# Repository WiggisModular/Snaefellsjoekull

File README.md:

** Prodution files out of date, pots go the wrong way round. **

A simple modular eurorack stereo mixer.

## Modules

### panMonoCannel

* Panning mono channel

### MainNoFx

* A main out, 2 separate pots for out Volume.
* No FX send and return 

## Production Files and Documentation

See release tab

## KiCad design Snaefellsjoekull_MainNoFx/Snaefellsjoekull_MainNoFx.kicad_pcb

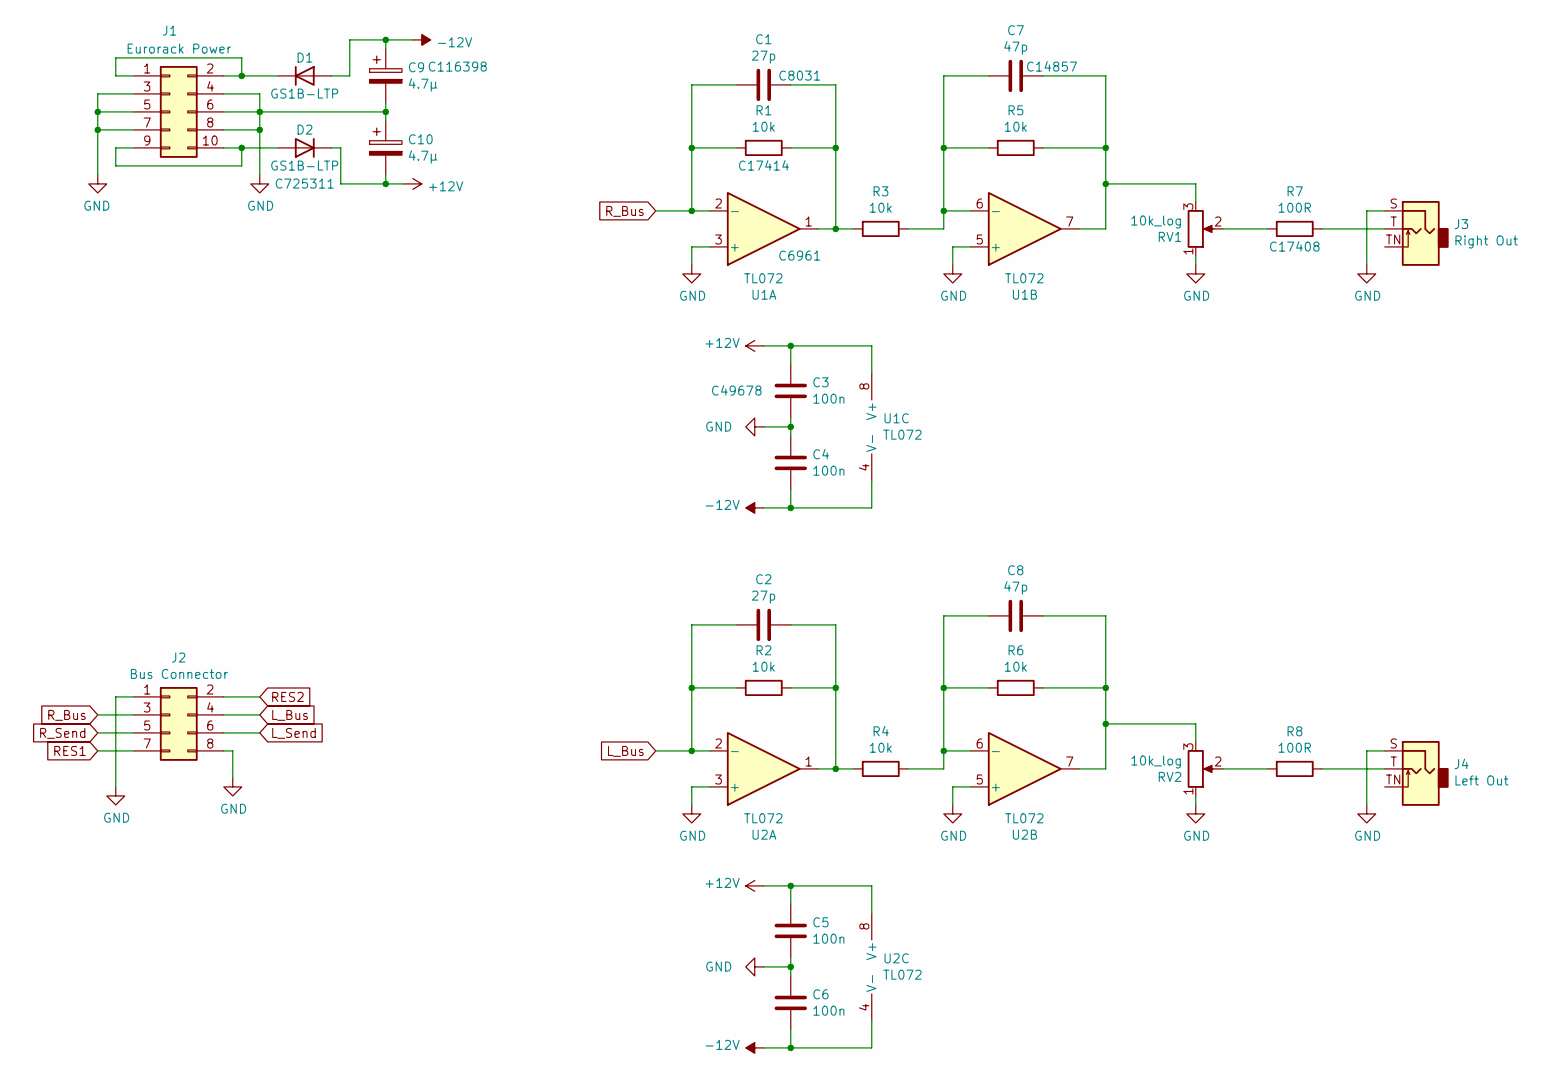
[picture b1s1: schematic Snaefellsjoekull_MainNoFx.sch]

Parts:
C1, C2: 27p; C_0805_2012Metric_Pad1.18x1.45mm_HandSolder; LCSC C8031
C3, C4, C5, C6: 100n; C_0805_2012Metric_Pad1.18x1.45mm_HandSolder; LCSC C49678
C7, C8: 47p; C_0805_2012Metric_Pad1.18x1.45mm_HandSolder; LCSC C14857
C9, C10: 4.7µ; CP_Elec_4x5.8; LCSC C116398
D1, D2: GS1B-LTP; D_SMA-SMB_Universal_Handsoldering; LCSC C725311
J1: Eurorack Power; PinHeader_2x05_P2.54mm_Vertical
J2: Bus Connector; PinHeader_2x04_P2.54mm_Vertical
J3: Right Out; Jack_3.5mm_QingPu_WQP-PJ398SM_Vertical_CircularHoles
J4: Left Out; Jack_3.5mm_QingPu_WQP-PJ398SM_Vertical_CircularHoles
R1, R2, R3, R4, R5, R6: 10k; R_0805_2012Metric_Pad1.20x1.40mm_HandSolder; LCSC C17414
R7, R8: 100R; R_0805_2012Metric_Pad1.20x1.40mm_HandSolder; LCSC C17408
RV1, RV2: 10k_log; Potentiometer_Alpha_RD901F-40-00D_Single_Vertical_CircularH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
U1, U2: TL072; SOIC-8_3.9x4.9mm_P1.27mm; LCSC C6961

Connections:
+12V: C3.1, C5.1, C10.2, D2.1 (K), U1.8 (V+), U2.8 (V+)
-12V: C4.2, C6.2, C9.1, D1.2 (A), U1.4 (V-), U2.4 (V-)
GND: C3.2, C4.1, C5.2, C6.1, C9.2, C10.1, J1.3, J1.4, J1.5, J1.6, J1.7, J1.8, J2.1, J2.8, J3.S, J4.S, RV1.1, RV2.1, U1.3 (+), U1.5 (+), U2.3 (+), U2.5 (+)
L_Bus: C2.1, J2.4, R2.2, U2.2 (-)
L_Send: J2.6
unnamed: C1.2, R1.1, R3.2, U1.1
unnamed: C2.2, R2.1, R4.2, U2.1
unnamed: C7.1, R3.1, R5.2, U1.6 (-)
unnamed: C7.2, R5.1, RV1.3, U1.7
unnamed: C8.1, R4.1, R6.2, U2.6 (-)
unnamed: C8.2, R6.1, RV2.3, U2.7
unnamed: D1.1 (K), J1.1, J1.2
unnamed: D2.2 (A), J1.9, J1.10
unnamed: J3.T, R7.1
unnamed: J4.T, R8.1
unnamed: R7.2, RV1.2
unnamed: R8.2, RV2.2
RES1: J2.7
RES2: J2.2
R_Bus: C1.1, J2.3, R1.2, U1.2 (-)
R_Send: J2.5

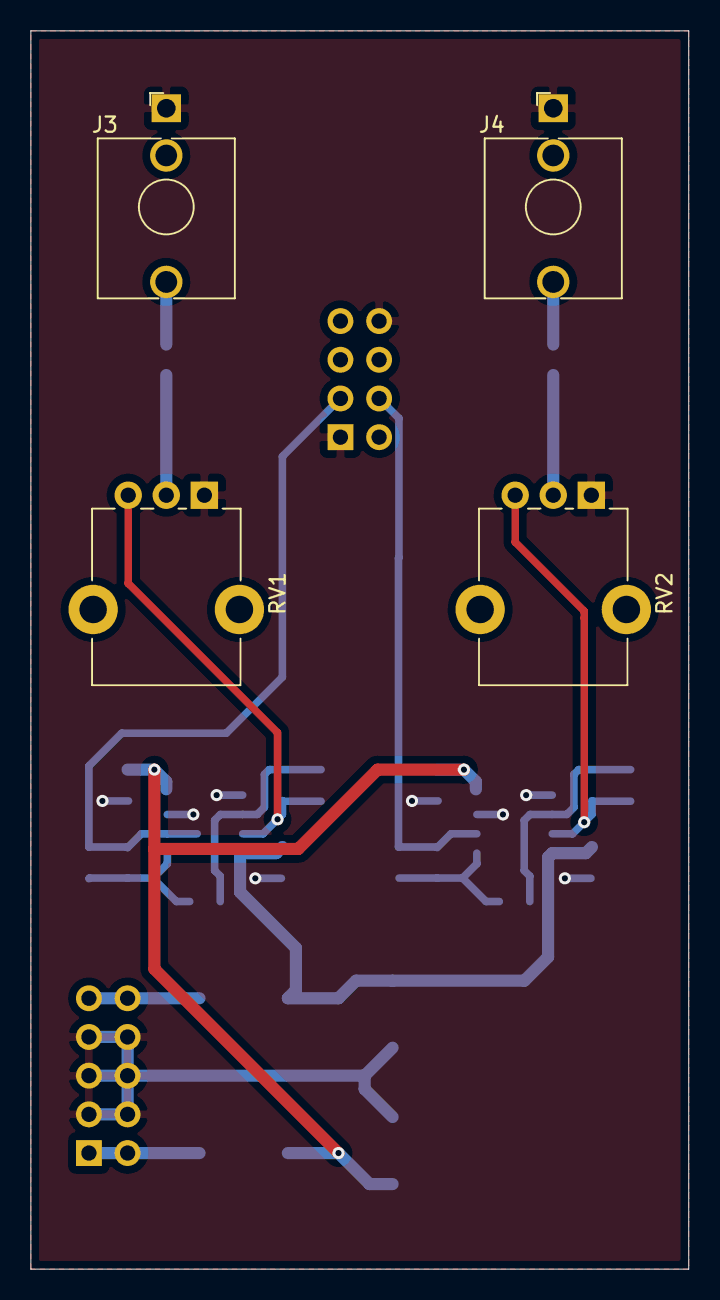
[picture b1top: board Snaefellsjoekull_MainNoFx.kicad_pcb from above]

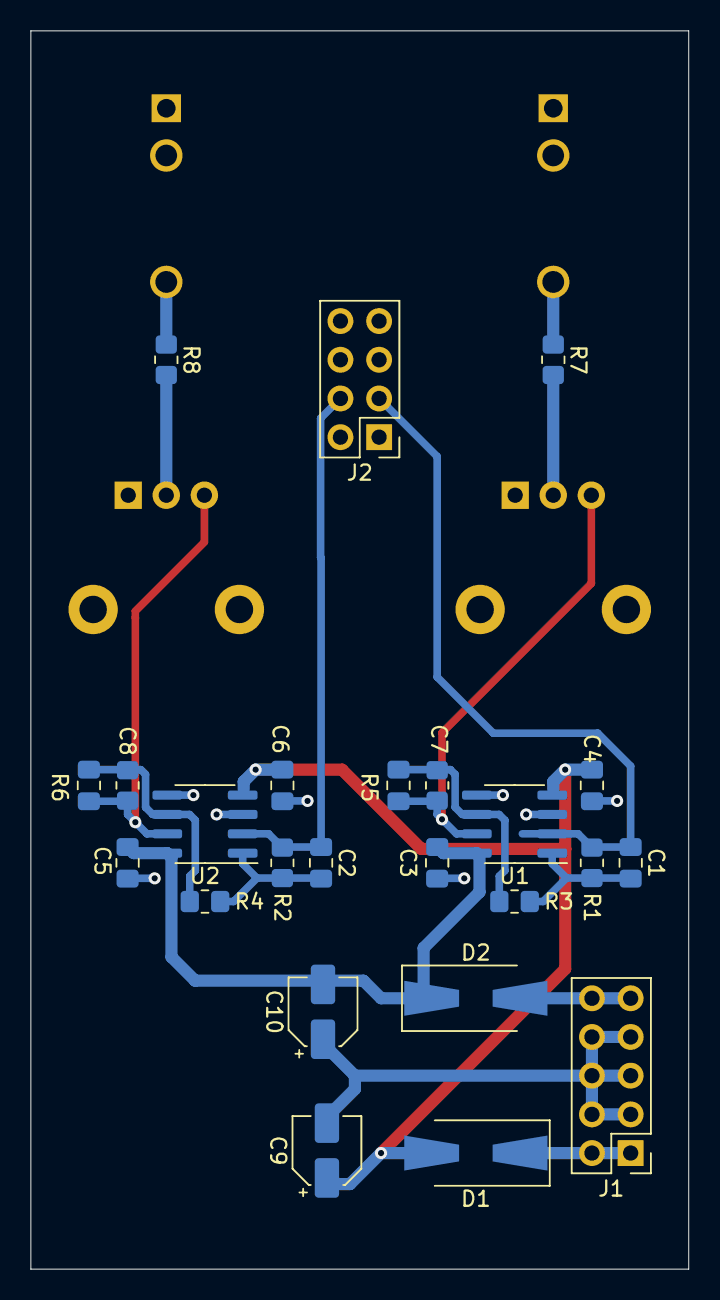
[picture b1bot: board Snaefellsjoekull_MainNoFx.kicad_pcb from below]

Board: 2 copper layers, 43.2 x 81.3 mm, 28 parts (24 on the bottom side), 17 nets.

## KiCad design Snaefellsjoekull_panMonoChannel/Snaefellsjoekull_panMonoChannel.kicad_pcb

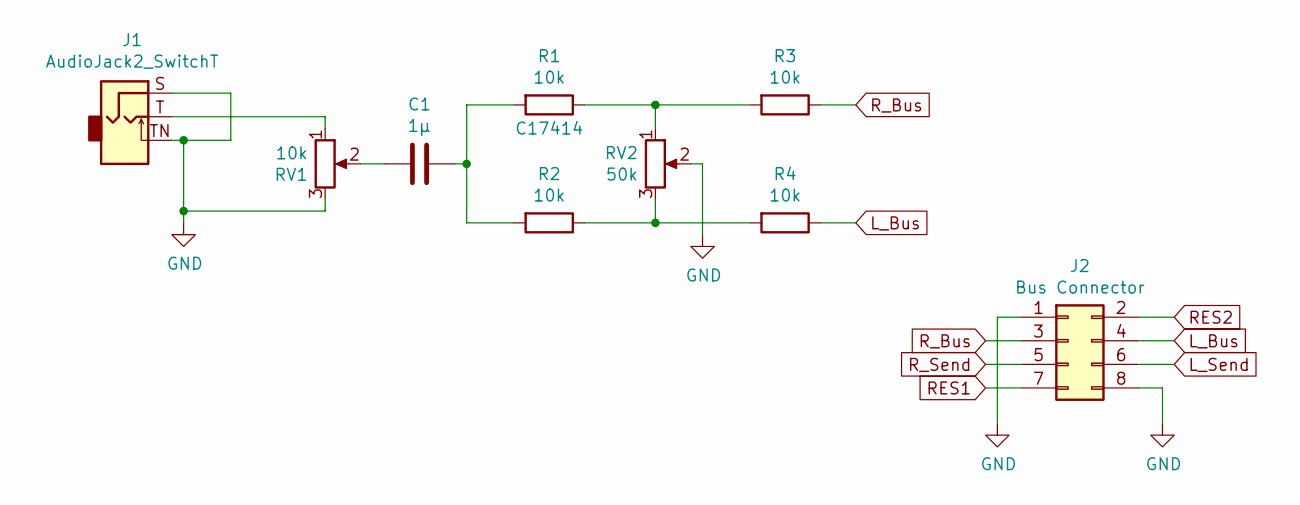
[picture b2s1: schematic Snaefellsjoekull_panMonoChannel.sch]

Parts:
C1: 1µ; C_0805_2012Metric_Pad1.18x1.45mm_HandSolder; LCSC C28323
J1: AudioJack2_SwitchT; Jack_3.5mm_QingPu_WQP-PJ398SM_Vertical_CircularHoles
J2: Bus Connector; PinHeader_2x04_P2.54mm_Vertical
R1, R2, R3, R4: 10k; R_1206_3216Metric_Pad1.30x1.75mm_HandSolder; LCSC C17414
RV1: 10k; Potentiometer_Bourns_PTV09A-1_Single_Vertical
RV2: 50k; Potentiometer_Bourns_PTV09A-1_Single_Vertical

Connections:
GND: J1.S, J1.TN, J2.1, J2.8, RV1.3, RV2.2
L_Bus: J2.4, R4.1
L_Send: J2.6
unnamed: C1.1, R1.2, R2.2
unnamed: C1.2, RV1.2
unnamed: J1.T, RV1.1
unnamed: R1.1, R3.2, RV2.1
unnamed: R2.1, R4.2, RV2.3
RES1: J2.7
RES2: J2.2
R_Bus: J2.3, R3.1
R_Send: J2.5

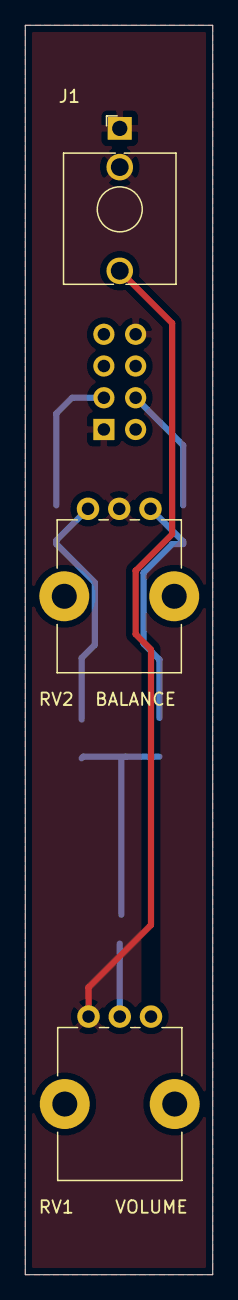
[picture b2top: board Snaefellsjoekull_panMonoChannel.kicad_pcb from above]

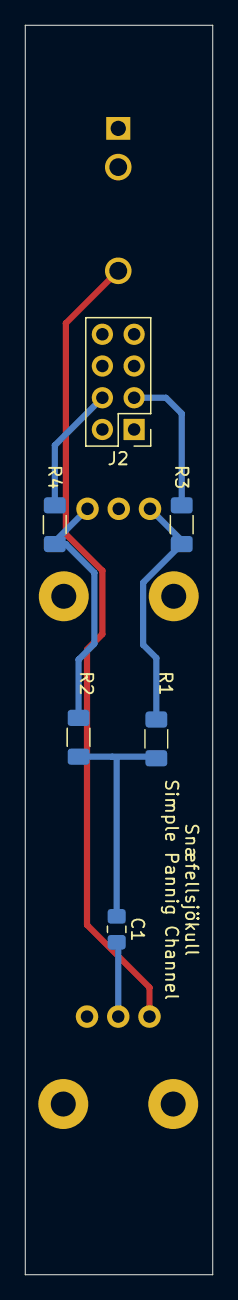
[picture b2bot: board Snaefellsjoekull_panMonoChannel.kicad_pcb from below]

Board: 2 copper layers, 15.0 x 100.0 mm, 9 parts (6 on the bottom side), 8 nets.

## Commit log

2021-02-08 Inital data commit
2021-02-08 Updated Project files
2021-02-08 readme
2021-03-05 Panel generator added
2021-03-05 main pos inplemented
2021-03-05 added dimensions
2021-03-06 modularized openscad
2021-03-06 generated dxf
2021-03-06 PCB updated
2021-03-07 fixed standard values
2021-03-07 Potentiometer fixed
2021-03-07 Readme updated
2021-03-07 data update
